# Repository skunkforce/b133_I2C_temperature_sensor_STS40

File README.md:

# edgy_board number b133
This design is part of the [edgy board project](https://github.com/skunkforce/edgy_boards). It provides the functionality of a tiny I2C temperature sensor STS40. 

# getting started
This repository uses submodules. After cloning use the command 

```$ git submodule update --init --recursive```

to pull the submodules before opening the project with kicad. 

# Tests
Tests can be found in [TESTS.md](TESTS.md)

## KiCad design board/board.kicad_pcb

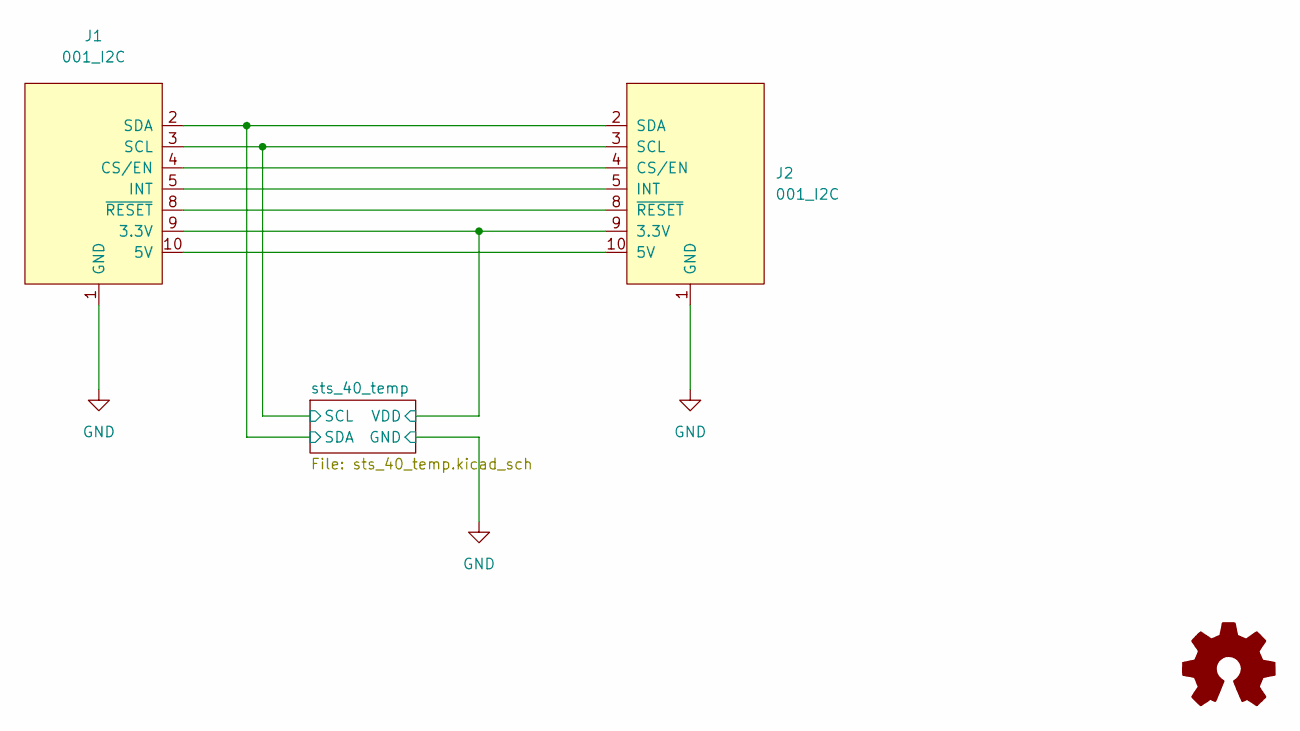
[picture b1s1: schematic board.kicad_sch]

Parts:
J1: 001_I2C; on_edge_2x05_device
J2: 001_I2C; on_edge_2x05_host
LOGO1: Logo_Open_Hardware_Small; OSHW-Symbol_6.7x6mm_SilkScreen

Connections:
/sts_40_temp/SCL: J1.3 (SCL), J2.3 (SCL); also elsewhere on the board
/sts_40_temp/SDA: J1.2 (SDA), J2.2 (SDA); also elsewhere on the board
/sts_40_temp/VDD: J1.9 (3.3V), J2.9 (3.3V); also elsewhere on the board
GND: J1.1 (GND), J2.1 (GND); also elsewhere on the board
unnamed: J1.4 (CS/EN), J2.4 (CS/EN)
unnamed: J1.5 (INT), J2.5 (INT)
unnamed: J1.8 (~RESET), J2.8 (~RESET)
unnamed: J1.10 (5V), J2.10 (5V)

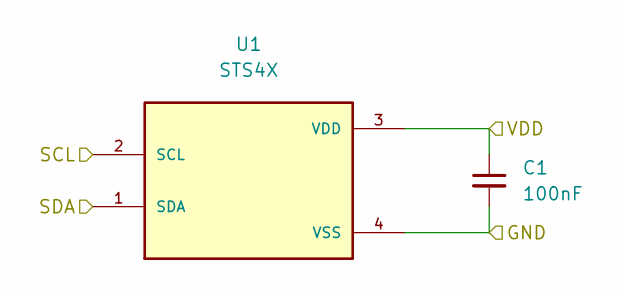
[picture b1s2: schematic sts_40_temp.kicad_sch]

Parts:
C1: 100nF; C_0402_1005Metric
U1: STS4X

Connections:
/sts_40_temp/SCL: U1.2 (SCL); also elsewhere on the board
/sts_40_temp/SDA: U1.1 (SDA); also elsewhere on the board
/sts_40_temp/VDD: C1.1, U1.3 (VDD); also elsewhere on the board
GND: C1.2, U1.4 (VSS); also elsewhere on the board

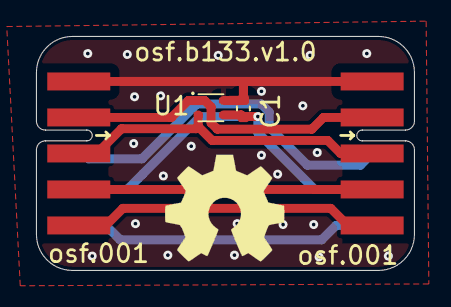
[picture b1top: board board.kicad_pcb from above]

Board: 2 copper layers, 21.0 x 13.0 mm, 5 parts (0 on the bottom side), 8 nets.

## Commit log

2023-05-17 initial
